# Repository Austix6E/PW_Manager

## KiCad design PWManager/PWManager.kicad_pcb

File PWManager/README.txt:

Project: PWManager
Engineer: Austin Cole
Email: austi01101110@gmail.com

********************************************************************************

Dimensions:
X = 35.25
Y = 64.75

Layer Count = 2
Thickness = 0.062"
Copper Wt. = 1 oz
Silkscreen: Top Side

Files:

.GBL    Bottom Copper
.GBS    Bottom Soldermask
.GTL    Top Copper
.GTO    Top Silkscreen
.GTS    Top Soldermask
.GM1	Board Outline
.DRL    Binary Drill File
.GTP	Top Paste - for stencil

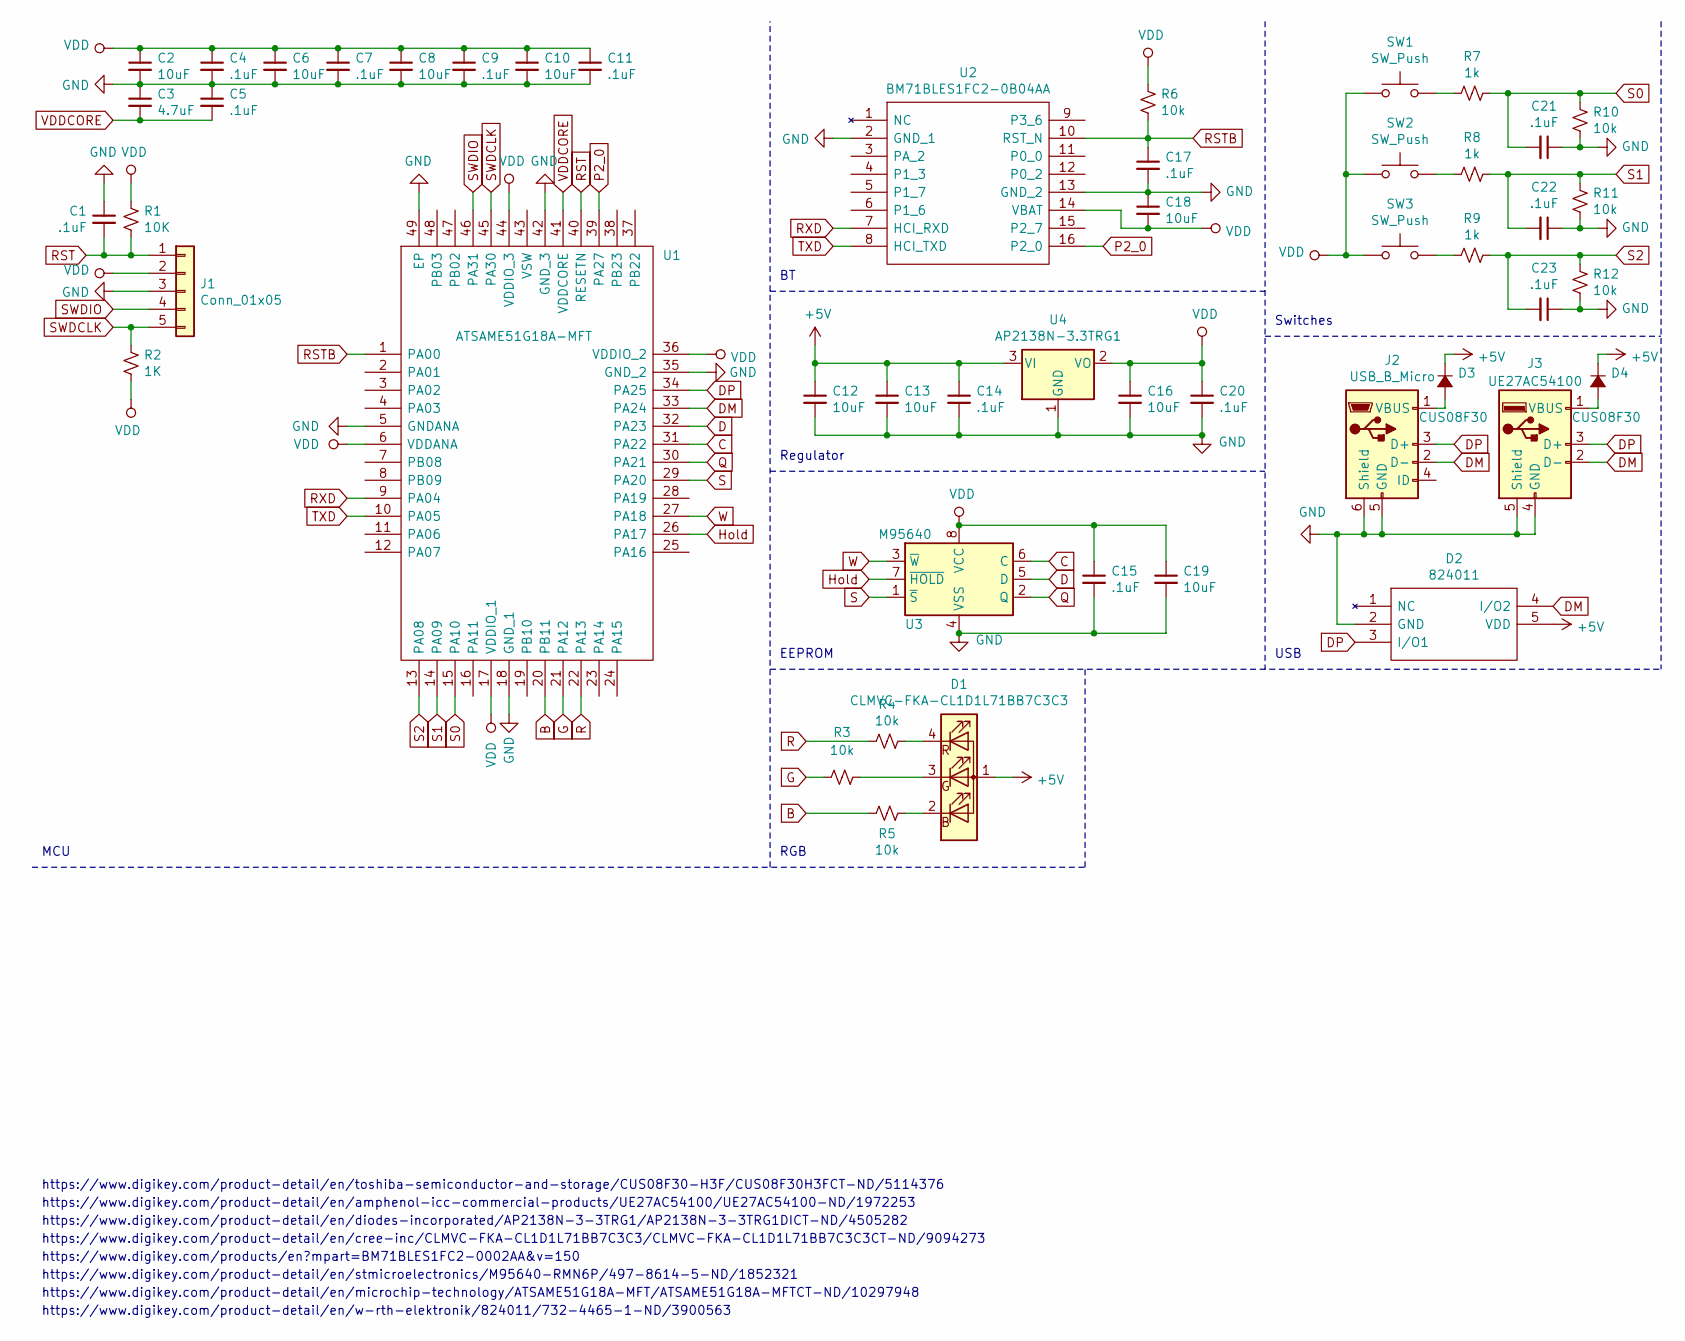
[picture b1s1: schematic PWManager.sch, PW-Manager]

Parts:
C1, C4, C5, C7, C9, C11, C14, C15, C17, C20, C21, C22, C23: .1uF; C_0603_1608Metric
C2, C6, C8, C10, C12, C13, C16, C18, C19: 10uF; C_0805_2012Metric
C3: 4.7uF; C_0805_2012Metric
D1: CLMVC-FKA-CL1D1L71BB7C3C3; CLMVCFKACL1D1L71BB7C3C3
D2: 824011; SOT-23-5; Mouser Part Number 710-824011
D3, D4: CUS08F30; D_SOD-323
J1: Conn_01x05; PinHeader_1x05_P2.54mm_Vertical
J2: USB_B_Micro; USB_Micro-B_Molex-105017-0001
J3: UE27AC54100; USB_A_Stewart_SS-52100-001_Horizontal
R1: 10K; R_0603_1608Metric
R2: 1K; R_0603_1608Metric
R3, R4, R5, R6, R10, R11, R12: 10k; R_0603_1608Metric
R7, R8, R9: 1k; R_0603_1608Metric
SW1, SW2, SW3: SW_Push; SW_PUSH_6mm_H8.5mm
U1: ATSAME51G18A-MFT; QFN50P700X700X90-49N-D; Mouser Part Number 556-ATSAME51G18A-MFT
U2: BM71BLES1FC2-0B04AA; BM71BLES1FC2_1; Mouser Part Number 579-BM71BS1FC2-BB04
U3: M95640; SOIC-8_3.9x4.9mm_P1.27mm
U4: AP2138N-3.3TRG1; SOT-23

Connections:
+5V: C12.1, C13.1, C14.1, D1.1 (A), D2.5 (VDD), D3.1 (K), D4.1 (K), U4.3 (VI)
B: R5.2, U1.20 (PB11)
C: U1.31 (PA22), U3.6 (C)
D: U1.32 (PA23), U3.5 (D)
DM: D2.4 (I/O2), J2.2 (D-), J3.2 (D-), U1.33 (PA24)
DP: D2.3 (I/O1), J2.3 (D+), J3.3 (D+), U1.34 (PA25)
G: R3.2, U1.21 (PA12)
GND: C1.1, C2.2, C3.1, C4.2, C5.1, C6.2, C7.2, C8.2, C9.2, C10.2, C11.2, C12.2, C13.2, C14.2, C15.2, C16.2, C17.2, C18.1, C19.2, C20.2, C21.1, C22.1, C23.1, D2.2 (GND), J1.3, J2.5 (GND), J2.6 (Shield), J3.4 (GND), J3.5 (Shield), R10.1, R11.1, R12.1, U1.5 (GNDANA), U1.18 (GND_1), U1.35 (GND_2), U1.42 (GND_3), U1.49 (EP), U2.2 (GND_1), U2.13 (GND_2), U3.4 (VSS), U4.1 (GND)
Hold: U1.26 (PA17), U3.7 (~HOLD)
unnamed: D1.2 (BK), R5.1
unnamed: D1.3 (GK), R3.1
unnamed: D1.4 (RK), R4.1
unnamed: D3.2 (A), J2.1 (VBUS)
unnamed: D4.2 (A), J3.1 (VBUS)
unnamed: R7.2, SW1.2
unnamed: R8.2, SW2.2
unnamed: R9.2, SW3.2
P2_0: U1.39 (PA27), U2.16 (P2_0)
Q: U1.30 (PA21), U3.2 (Q)
R: R4.2, U1.22 (PA13)
RST: C1.2, J1.1, R1.2, U1.40 (RESETN)
RSTB: C17.1, R6.2, U1.1 (PA00), U2.10 (RST_N)
RXD: U1.9 (PA04), U2.7 (HCI_RXD)
S: U1.29 (PA20), U3.1 (~S)
S0: C21.2, R7.1, R10.2, U1.15 (PA10)
S1: C22.2, R8.1, R11.2, U1.14 (PA09)
S2: C23.2, R9.1, R12.2, U1.13 (PA08)
SWDCLK: J1.5, R2.1, U1.45 (PA30)
SWDIO: J1.4, U1.46 (PA31)
TXD: U1.10 (PA05), U2.8 (HCI_TXD)
VDD: C2.1, C4.1, C6.1, C7.1, C8.1, C9.1, C10.1, C11.1, C15.1, C16.1, C18.2, C19.1, C20.1, J1.2, R1.1, R2.2, R6.1, SW1.1, SW2.1, SW3.1, U1.6 (VDDANA), U1.17 (VDDIO_1), U1.36 (VDDIO_2), U1.44 (VDDIO_3), U2.14 (VBAT), U3.8 (VCC), U4.2 (VO)
VDDCORE: C3.2, C5.2, U1.41 (VDDCORE)
W: U1.27 (PA18), U3.3 (~W)

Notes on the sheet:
https://www.digikey.com/product-detail/en/microchip-technology/ATSAME51G18A-MFT/ATSAME51G18A-MFTCT-ND/10297948
https://www.digikey.com/product-detail/en/stmicroelectronics/M95640-RMN6P/497-8614-5-ND/1852321
https://www.digikey.com/products/en?mpart=BM71BLES1FC2-0002AA&v=150
USB
MCU
https://www.digikey.com/product-detail/en/w-rth-elektronik/824011/732-4465-1-ND/3900563
Regulator
EEPROM
RGB
Switches
https://www.digikey.com/product-detail/en/cree-inc/CLMVC-FKA-CL1D1L71BB7C3C3/CLMVC-FKA-CL1D1L71BB7C3C3CT-ND/9094273
https://www.digikey.com/product-detail/en/diodes-incorporated/AP2138N-3-3TRG1/AP2138N-3-3TRG1DICT-ND/4505282
https://www.digikey.com/product-detail/en/amphenol-icc-commercial-products/UE27AC54100/UE27AC54100-ND/1972253
https://www.digikey.com/product-detail/en/toshiba-semiconductor-and-storage/CUS08F30-H3F/CUS08F30H3FCT-ND/5114376

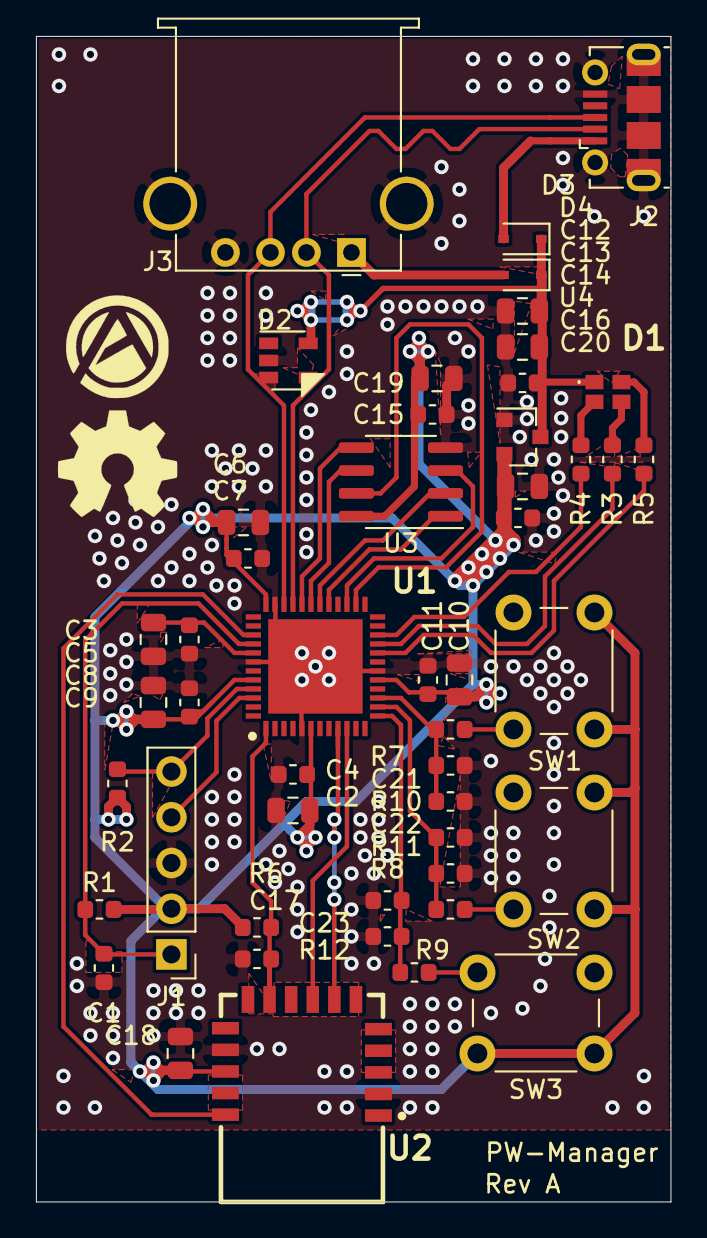
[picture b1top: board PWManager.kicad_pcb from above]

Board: 2 copper layers, 35.2 x 64.8 mm, 49 parts (0 on the bottom side), 33 nets.

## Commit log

2020-05-03 Init 20-5-3-0210
2020-05-10 Rev A Board
